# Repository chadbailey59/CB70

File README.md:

# CB70: A Split, Staggered Wireless Keyboard

- Supports MX and Choc switches
- Dual-wireless, powered by Nice!Nano v2's and ZMK
- Compatible with lots of popular keysets

Why CB70? It's my initials, and it used to be a 70-key layout. When I deleted a key, changing the name to The Joke Number just seemed too obvious.

## What's Available

- KiCAD files for the combo MX/Choc PCBs in `/PCB`
- [Keyboard Layout Editor](http://www.keyboard-layout-editor.com/) JSON for the MX and Choc versions in `/KLE`
- Config files for the ZMK firmware in `/ZMK`, and pre-compiled firmware in `/Firmware`
- OnShape docs for three different cases: [MX](https://cad.onshape.com/documents/61077a70c0807a2f741d218a/w/b756240a5bc81a242d3100ae/e/06f8d761157dde9586b0a508), [Choc](https://cad.onshape.com/documents/518ea40d790487622d23318b/w/b5c85f466e1f1d2c95445d69/e/3acfa7d78165eaa4fb25c29e), and [Choc Slim](https://cad.onshape.com/documents/839a1d1e7ccef3f6cb852ad6/w/885d6dd90bac1c92721256f6/e/4149e8558c641b31c0ba8e37)
- STL files for the 3 different case styles in `/Case`

### Update 2025-08-24: The Dongle Variant

ZMK recently added support for [dongles!](https://zmk.dev/docs/development/hardware-integration/dongle) There are now two versions of the firmware and ZMK source. The `non-dongle` folder is the traditional CB70, with two nice!nanos—one for the left half, one for the right. The `dongle` version actually requires _three_ nice!nanos (or whatever boards you're using): Two for the left and right halves, and one for the 'dongle'.

The main benefit of the dongle version (for me) is that it's easier to switch the whole keyboard to another computer by just plugging in the dongle.

## The Philosophy

The key layout is based around something I've been honing for almost five years now. I've tried a few different ortho/ergo layouts, but contrary to what the internet says, they always slow me down way too much. Meanwhile, I use this at my desk, I still use my MacBook Pro's built-in keyboard a lot, and I average 110-120 WPM on both.

A few thoughts on the layout:

I wanted to maintain parity between my keyboard and my MacBook Pro's keyboard as much as possible, so I don't do much with ZMK itself. Rather, I use [Karabiner-elements](https://karabiner-elements.pqrs.org/) to make many of these 'tricks' work for both my custom keyboard and my MacBook Pro.

I've found I never use my left thumb for the space bar, so I placed a Shift key where my left thumb naturally falls. I fell in love with this almost immediately, and it's the first thing I miss when typing on my MacBook Pro. I've tried a few different Karabiner-elements hacks to attempt to replicate this for the MBP's built-in space bar, but none of them work that well.

I use the Caps Lock key as an additional Command key with my left pinky, which you'll see in the Choc keyset. That's remapped in Karabiner-elements so it works both places.

The bottom-left key is a "Function" key, but I use a Karabiner-elements complex modification called "Map Function to Hyper when held" to give me a bunch of custom shortcuts. I can't figure out how to share that directly here.

The bottom-right Backspace key is remapped to Option-Backspace, which deletes a word. This is maybe my single favorite thing I've ever done on a computer. If I'm writing in Slack and realize I want to reword the last few words I typed, it's a super quick way to delete a word at a time.

The left column gives me a dedicated Esc key, and the other three are remapped to volume up/down, and a play/pause key.

## Building Your Own

### Switches and Stabilizers

You'll need at least 69 switches, either 2-pin MX or Choc. If you use MX switches, you'll need 4 plate-mount stabilizers, [such as these](https://www.amazon.com/DUROCK-Stabilizer-Keyboard-Stabilizers-Compatible/dp/B0CRRHP9MY/). The Choc version doesn't use any stabilizers.

### Keycaps

You can get the same Choc keycaps you see in the picture from [FK Caps' Custom Shop](https://fkcaps.com/custom/1VP7N2) if you want.

For Choc switches, you'll need 60 1u keycaps, and 9 1.5u keycaps.

For MX switches, you should be able to get by with a pretty standard TKL or 70% keyset (that's by design). The only 'weird' keys are:

- 1.75u right Shift key
- 1.5u Backspace key in the bottom row
- 2u space bar
- 1.25u Shift key for your left thumb

The pictured MX version is the [MT3 Susuwatari keyset](https://drop.com/buy/drop-matt3o-mt3-susuwatari-custom-keycap-set?defaultSelectionIds=952681) from Drop, with the Base kit covering everything except the 2u space bar (which I added from the "Spacebars" kit).

### Other Supplies

- 12 [M3 x 4mm heat set inserts](https://www.amazon.com/gp/product/B09MCWTBCC)
- 12 M3 x 8mm screws
- 69 [1N4148 diodes](https://www.amazon.com/gp/product/B07Q4F3Y5W/ref=ppx_yo_dt_b_search_asin_title?ie=UTF8&psc=1)
- 2 [3.7V batteries with JST-PHR-02 connectors](https://www.amazon.com/gp/product/B08VRYS8FT)
- 6 [JST 2.0mm connectors for the PCB](https://www.amazon.com/Taiss-Connector-Housing-Connectors-F-066-580PCS/dp/B0BHT1FQGY). The PCBs are spaced for the 2mm JST connectors, which are sometimes also called JST-PHR-02, like on the linked batteries.
- 2 nice!nano v2 boards
- [These round pin headers](https://www.amazon.com/Uxcell-a14081900ux0270-Single-Straight-Header/dp/B012ACSO4Y) to socket the nice!nanos
- Most people use diode legs to socket the nice!nanos, but if you want nicer pins, [these are the only ones I've found](https://www.amazon.com/dp/B0CKYKRSZ6?ref=ppx_yo2ov_dt_b_product_details&th=1).
- Some [push button switches](https://www.amazon.com/dp/B085SWHFMK?psc=1&ref=ppx_yo2ov_dt_b_product_details) and
  [SPST slide switches](https://www.amazon.com/dp/B09R43HCY3?psc=1&ref=ppx_yo2ov_dt_b_product_details) for reset and power. These particular ones can be wired to JST connectors for case mounting, or soldered directly into the PCB for low-profile setups.

### Assembly

Assembly should be pretty straightforward if you've built a keyboard before. The PCBs are marked for diode orientation. You'll want to make sure to install all of the diodes and the nice!nano sockets before installing any of the keyswitches. I also needed to snip the nice!nano socket legs flush with the PCB so the keyswitches mounted flat.

See the ZMK instructions for using GitHub actions to build the firmware yourself if you want to edit the keymaps.

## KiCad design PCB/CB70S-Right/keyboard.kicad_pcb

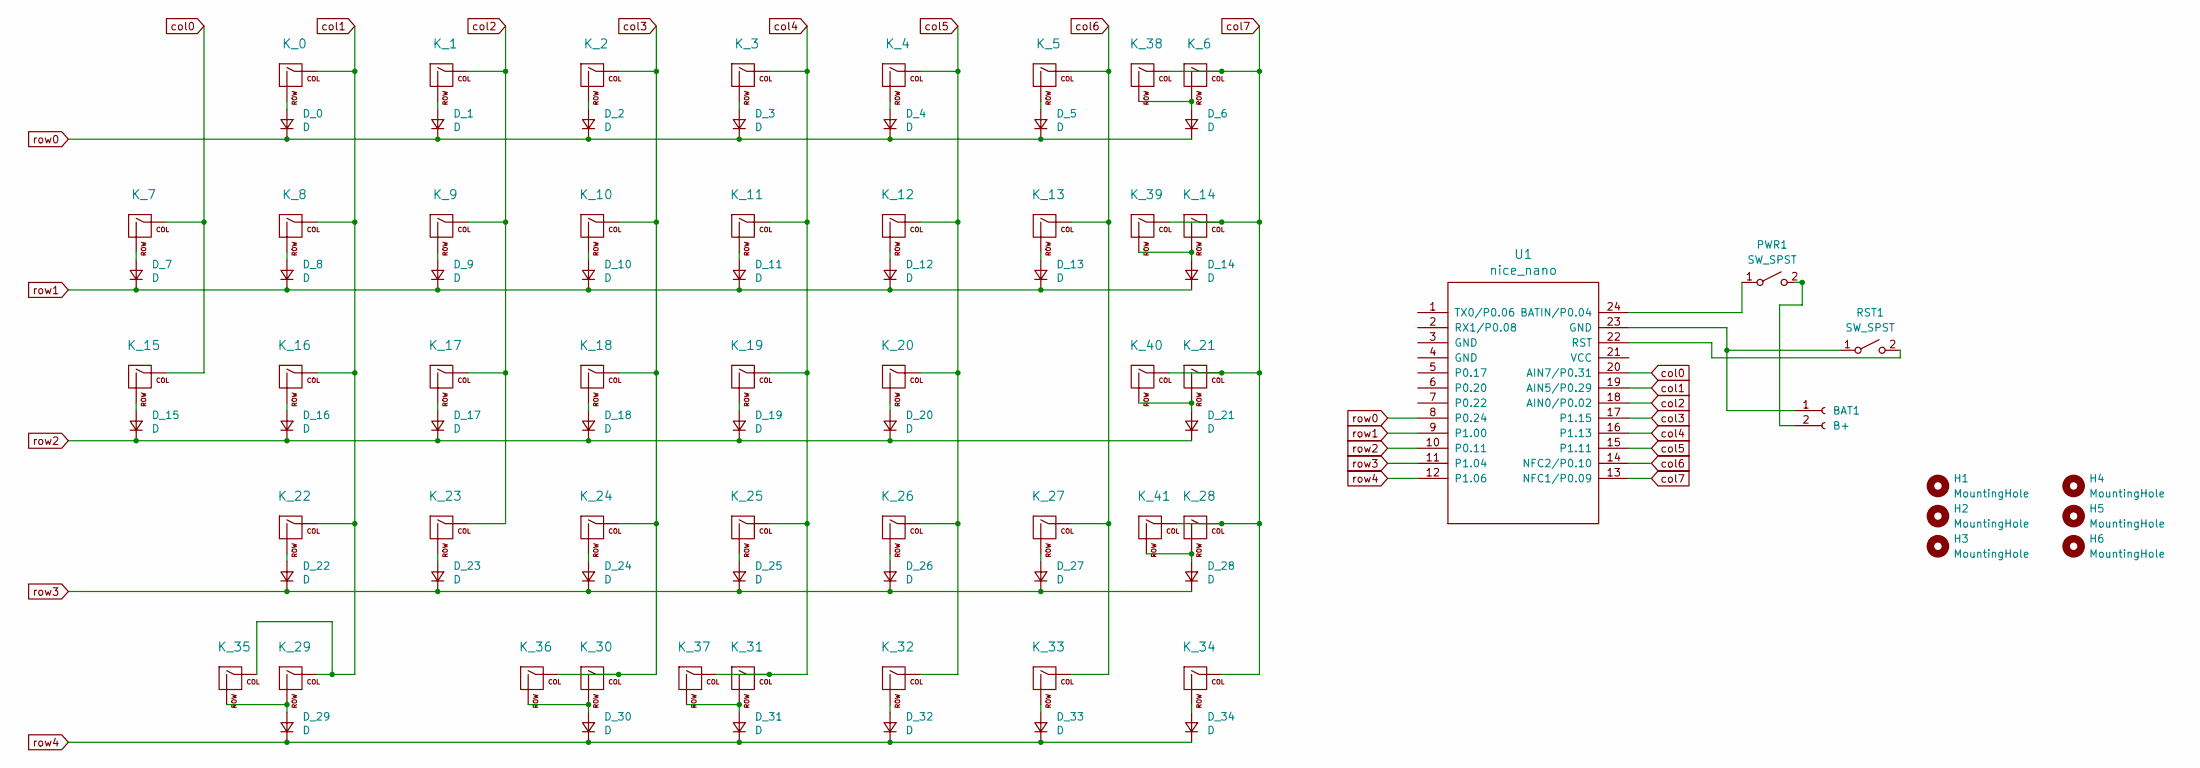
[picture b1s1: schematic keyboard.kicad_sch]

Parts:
BAT1: B+; JST_PH_B2B-PH-K_1x02_P2.00mm_Vertical
D_0, D_1, D_2, D_3, D_4, D_5, D_6, D_7, D_8, D_9, D_10, D_11, D_12, D_13, D_14, D_15, D_16, D_17, D_18, D_19, D_20, D_21, D_22, D_23, D_24, D_25, D_26, D_27, D_28, D_29, D_30, D_31, D_32, D_33, D_34: D; Diode_DO-35
H1, H2, H3, H4, H5, H6: MountingHole; MountingHole_3.2mm_M3
K_0, K_1, K_2, K_3, K_4, K_5, K_7, K_8, K_9, K_10, K_11, K_12, K_13, K_14, K_15, K_16, K_17, K_18, K_19, K_20, K_22, K_23, K_24, K_25, K_26, K_27, K_28, K_31, K_32, K_33, K_34, K_37: KEYSW; Choc-MX-19mm-1u
K_6, K_21, K_29, K_30, K_36, K_39: KEYSW; Choc-MX-19mm-1.5u
K_35, K_38: KEYSW; Choc-MX-19mm-2u
K_40: KEYSW; Choc-MX-19mm-2.25u
K_41: KEYSW; Choc-MX-19mm-1.75u
PWR1: SW_SPST; JST_PH_B2B-PH-K_1x02_P2.00mm_Vertical
RST1: SW_SPST; JST_PH_B2B-PH-K_1x02_P2.00mm_Vertical
U1: nice_nano; nice_nano_no_mid

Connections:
unnamed: BAT1.1, RST1.1 (A), U1.23 (GND)
unnamed: BAT1.2, PWR1.2 (B)
unnamed: D_0.2 (A), K_0.2 (ROW)
unnamed: D_1.2 (A), K_1.2 (ROW)
unnamed: D_2.2 (A), K_2.2 (ROW)
unnamed: D_3.2 (A), K_3.2 (ROW)
unnamed: D_4.2 (A), K_4.2 (ROW)
unnamed: D_5.2 (A), K_5.2 (ROW)
unnamed: D_6.2 (A), K_6.2 (ROW), K_38.2 (ROW)
unnamed: D_7.2 (A), K_7.2 (ROW)
unnamed: D_8.2 (A), K_8.2 (ROW)
unnamed: D_9.2 (A), K_9.2 (ROW)
unnamed: D_10.2 (A), K_10.2 (ROW)
unnamed: D_11.2 (A), K_11.2 (ROW)
unnamed: D_12.2 (A), K_12.2 (ROW)
unnamed: D_13.2 (A), K_13.2 (ROW)
unnamed: D_14.2 (A), K_14.2 (ROW), K_39.2 (ROW)
unnamed: D_15.2 (A), K_15.2 (ROW)
unnamed: D_16.2 (A), K_16.2 (ROW)
unnamed: D_17.2 (A), K_17.2 (ROW)
unnamed: D_18.2 (A), K_18.2 (ROW)
unnamed: D_19.2 (A), K_19.2 (ROW)
unnamed: D_20.2 (A), K_20.2 (ROW)
unnamed: D_21.2 (A), K_21.2 (ROW), K_40.2 (ROW)
unnamed: D_22.2 (A), K_22.2 (ROW)
unnamed: D_23.2 (A), K_23.2 (ROW)
unnamed: D_24.2 (A), K_24.2 (ROW)
unnamed: D_25.2 (A), K_25.2 (ROW)
unnamed: D_26.2 (A), K_26.2 (ROW)
unnamed: D_27.2 (A), K_27.2 (ROW)
unnamed: D_28.2 (A), K_28.2 (ROW), K_41.2 (ROW)
unnamed: D_29.2 (A), K_29.2 (ROW), K_35.2 (ROW)
unnamed: D_30.2 (A), K_30.2 (ROW), K_36.2 (ROW)
unnamed: D_31.2 (A), K_31.2 (ROW), K_37.2 (ROW)
unnamed: D_32.2 (A), K_32.2 (ROW)
unnamed: D_33.2 (A), K_33.2 (ROW)
unnamed: D_34.2 (A), K_34.2 (ROW)
unnamed: PWR1.1 (A), U1.24 (BATIN/P0.04)
unnamed: RST1.2 (B), U1.22 (RST)
col0: K_7.1 (COL), K_15.1 (COL), U1.20 (AIN7/P0.31)
col1: K_0.1 (COL), K_8.1 (COL), K_16.1 (COL), K_22.1 (COL), K_29.1 (COL), K_35.1 (COL), U1.19 (AIN5/P0.29)
col2: K_1.1 (COL), K_9.1 (COL), K_17.1 (COL), K_23.1 (COL), U1.18 (AIN0/P0.02)
col3: K_2.1 (COL), K_10.1 (COL), K_18.1 (COL), K_24.1 (COL), K_30.1 (COL), K_36.1 (COL), U1.17 (P1.15)
col4: K_3.1 (COL), K_11.1 (COL), K_19.1 (COL), K_25.1 (COL), K_31.1 (COL), K_37.1 (COL), U1.16 (P1.13)
col5: K_4.1 (COL), K_12.1 (COL), K_20.1 (COL), K_26.1 (COL), K_32.1 (COL), U1.15 (P1.11)
col6: K_5.1 (COL), K_13.1 (COL), K_27.1 (COL), K_33.1 (COL), U1.14 (NFC2/P0.10)
col7: K_6.1 (COL), K_14.1 (COL), K_21.1 (COL), K_28.1 (COL), K_34.1 (COL), K_38.1 (COL), K_39.1 (COL), K_40.1 (COL), K_41.1 (COL), U1.13 (NFC1/P0.09)
row0: D_0.1 (K), D_1.1 (K), D_2.1 (K), D_3.1 (K), D_4.1 (K), D_5.1 (K), D_6.1 (K), U1.8 (P0.24)
row1: D_7.1 (K), D_8.1 (K), D_9.1 (K), D_10.1 (K), D_11.1 (K), D_12.1 (K), D_13.1 (K), D_14.1 (K), U1.9 (P1.00)
row2: D_15.1 (K), D_16.1 (K), D_17.1 (K), D_18.1 (K), D_19.1 (K), D_20.1 (K), D_21.1 (K), U1.10 (P0.11)
row3: D_22.1 (K), D_23.1 (K), D_24.1 (K), D_25.1 (K), D_26.1 (K), D_27.1 (K), D_28.1 (K), U1.11 (P1.04)
row4: D_29.1 (K), D_30.1 (K), D_31.1 (K), D_32.1 (K), D_33.1 (K), D_34.1 (K), U1.12 (P1.06)

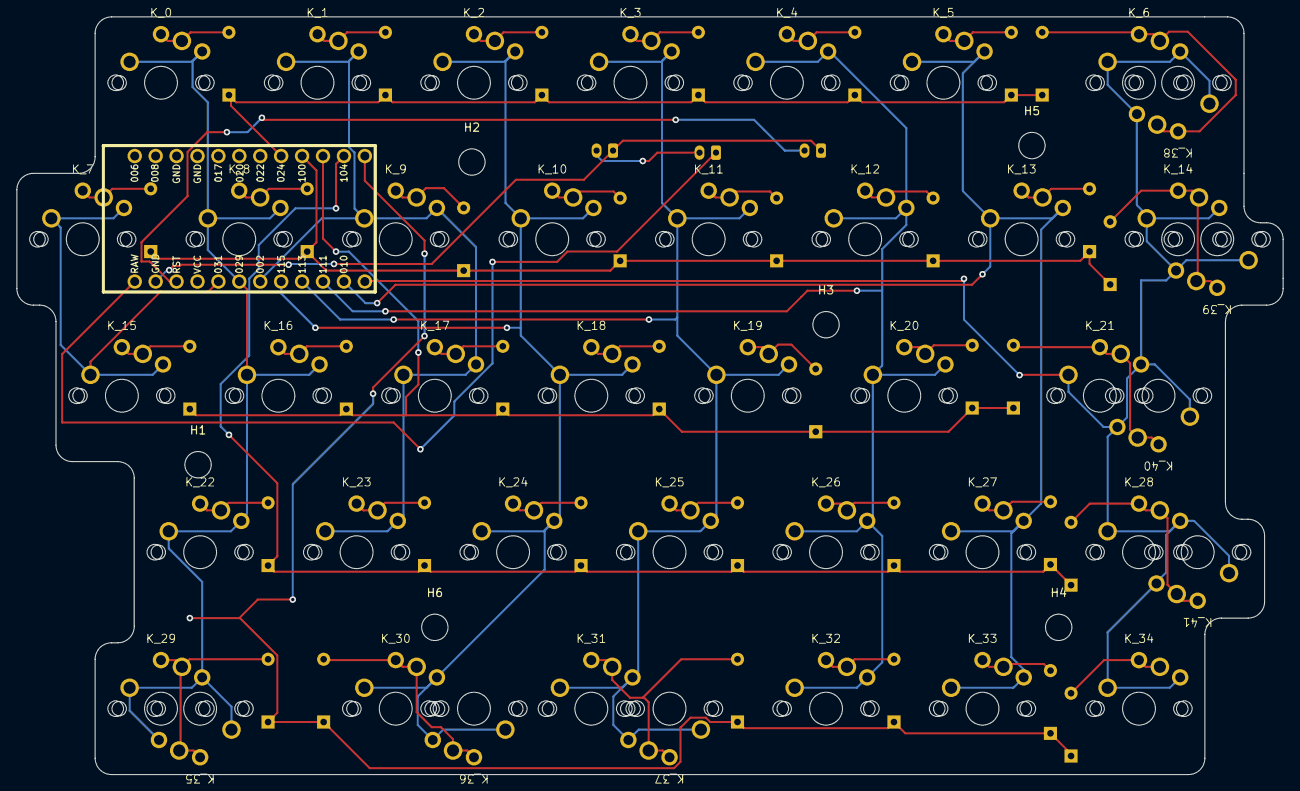
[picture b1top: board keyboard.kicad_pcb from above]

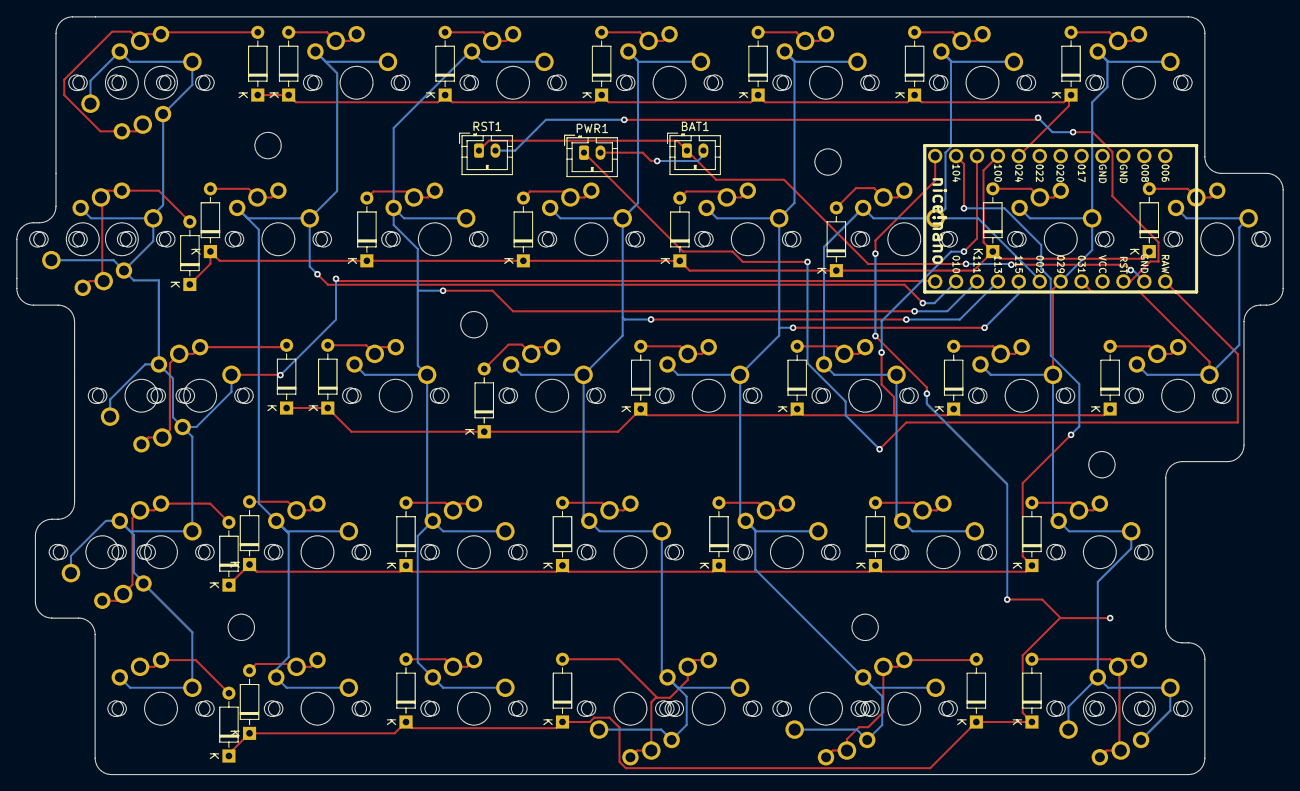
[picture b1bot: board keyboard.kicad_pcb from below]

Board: 2 copper layers, 153.8 x 92.0 mm, 87 parts (39 on the bottom side), 52 nets.

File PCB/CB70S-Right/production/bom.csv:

Designator,Footprint,Quantity,Value,LCSC Part #
BAT1,JST_PH_B2B-PH-K_1x02_P2.00mm_Vertical,1,B-,
"D_0, D_1, D_10, D_11, D_12, D_13, D_14, D_15, D_16, D_17, D_18, D_19, D_2, D_20, D_21, D_22, D_23, D_24, D_25, D_26, D_27, D_28, D_29, D_3, D_30, D_31, D_32, D_33, D_34, D_4, D_5, D_6, D_7, D_8, D_9",Diode_DO-35,35,D,
"K_0, K_1, K_10, K_11, K_12, K_13, K_14, K_15, K_16, K_17, K_18, K_19, K_2, K_20, K_22, K_23, K_24, K_25, K_26, K_27, K_28, K_3, K_31, K_32, K_33, K_34, K_37, K_4, K_5, K_7, K_8, K_9",Choc-MX-19mm-1u,32,KEYSW,
"K_21, K_29, K_30, K_36, K_39, K_6",Choc-MX-19mm-1.5u,6,KEYSW,
"K_35, K_38",Choc-MX-19mm-2u,2,KEYSW,
K_40,Choc-MX-19mm-2.25u,1,KEYSW,
K_41,Choc-MX-19mm-1.75u,1,KEYSW,
"PWR1, RST1",JST_PH_B2B-PH-K_1x02_P2.00mm_Vertical,2,SW_SPST,
U1,nice_nano_no_mid,1,nice_nano,

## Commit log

2025-08-24 added dongle mode
2025-08-24 fixing ZMK
2025-08-24 fixed zmk folder
